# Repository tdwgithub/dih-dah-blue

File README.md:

# Dih Dah Blue

**A Bluetooth LE wireless link between a Morse code (CW) paddle and a radio.**

Dih Dah Blue replaces the cable between your CW paddle and your radio with a pair of small battery-powered boards. The paddle-side board watches the paddle contacts and sends each transition over Bluetooth LE. The radio-side board drives a solid-state relay wired to the radio's key input. To your radio, it looks like the paddle is plugged straight in.

This repository holds the firmware, KiCad schematics and PCB layouts, and the 3D-printable enclosure described in the *Circuit Cellar* article **"Dih Dah Blue – Bluetooth Remote CW Key"** by Todd Wade, W8LEV.

## How it works

Both boards are built around the Seeed Studio XIAO ESP32-C6. The module provides a RISC-V high-power (HP) core and an ultra-low-power (ULP/LP) core, a built-in LiPo charger and a USB-C port for power and programming.

| | Paddle side | Radio side |
|---|---|---|
| BLE role | Central | Peripheral (advertises as `CW_Radio`) |
| Connects to | Paddle via 3-position terminal block (left, right, common) | Radio key input via 3-position terminal block, through an ASSR-1228 2-pole solid-state relay |
| Power strategy | ULP core watches the paddle while the HP core sleeps. HP core goes to light sleep after 2 min idle and deep sleep after 10 min | HP core only, light sleep when idle |
| Typical idle current | ~90 µA | ~17 mA |

**Paddle side:** The ULP core debounces the paddle inputs, places time-stamped events on a queue shared with the HP core, then wakes the HP core. The HP core re-establishes the BLE link if needed and sends each queued event to the radio side. While the link is idle, the HP core steps down from light sleep to deep sleep. A paddle tap wakes everything back up, and the LED blinks three times quickly once the link is up.

**Radio side:** Accepts the connection, receives paddle events and drives the relay outputs to match.

## Repository layout

```
firmware/
  paddle/     ESP-IDF project: HP core (main/main.c) + ULP core (main/ulp/)
  radio/      ESP-IDF project: radio-side BLE peripheral
hardware/
  paddle/     KiCad project, schematic PDF and BOM for the paddle-side board
  radio/      KiCad project, schematic PDF and BOM for the radio-side board
  panel/      Both boards panelized into one 2-up panel, with ready-to-order Gerbers
enclosure/    OpenSCAD source and STL for the shared enclosure
docs/images/  Photos and renders
```

## Building the hardware

Each board is 2" × 2" and uses only through-hole parts. You can also build the circuits on a breadboard or stripboard.

- **Schematics:** [`hardware/paddle/Paddle-schematic.pdf`](hardware/paddle/Paddle-schematic.pdf) and [`hardware/radio/radio-schematic.pdf`](hardware/radio/radio-schematic.pdf)
- **Bills of materials:** [`hardware/paddle/Paddle-BOM.csv`](hardware/paddle/Paddle-BOM.csv) and [`hardware/radio/radio-BOM.csv`](hardware/radio/radio-BOM.csv)
- **Ordering PCBs:** Upload [`hardware/panel/dihdah_blue_r2-gerbers.zip`](hardware/panel/dihdah_blue_r2-gerbers.zip) to JLCPCB, PCBWay or a similar board house. It holds both boards on a single panel joined by mouse-bite tabs. Snap them apart and sand the edges.

**Assembly notes:**

1. Solder the low-profile parts first (resistors and capacitors), then the battery connector, then the buttons.
2. If you'll use the enclosure, bend the LED leads 90° about 1/8" above the board so the LED pokes through the enclosure hole. The cathode goes to the square pad nearest the board edge.
3. **Install the XIAO module last.** Its battery and RESET/EN and BOOT connections are only on pads underneath the module. *Before* soldering the module down, solder four wires to the **Battery +**, **Battery −**, **Reset/EN** and **Option/BOOT** pads on its underside. Route the wires out from under the edge opposite the USB-C connector. Then solder the module's header pins, trim the wires and solder them to the four labeled holes near the battery connector.

> **Article correction:** The article text says R2 and R3 are the paddle input pull-ups and R1 is the LED resistor. On both boards **R3 (1K) is the LED resistor**. On the paddle side, **R1 and R2 (100K) are the paddle input pull-ups**. The schematics (Figures 1 and 2), the PCBs and the files here are correct.

**Battery:** Either board runs from a single-cell 3.7 V LiPo (the author uses Adafruit's 500 mAh flat pack) or directly from USB-C. Buy batteries from a reputable supplier. A slot in the PCB lets the battery lead pass up from below the board.

> **Radio-side note:** The relay output is meant for "dry contact" key inputs on radios or keyers with a built-in electronic keyer. Don't connect it to older rigs that put a voltage on the key line.

## Building the firmware

Requires [ESP-IDF](https://docs.espressif.com/projects/esp-idf/en/v5.3.4/esp32c6/get-started/) **v5.3.x** (developed on v5.3.4).

```sh
cd firmware/radio        # or firmware/paddle
idf.py set-target esp32c6
idf.py build
idf.py -p <serial-port> flash monitor
```

The paddle project builds the ULP program in `main/ulp/` and embeds it into the HP-core image automatically.

To force a XIAO into the bootloader, hold **BOOT** (SW2) while pressing **RESET/EN** (SW1).

### Current limitations / ideas for future versions

- The paddle mode is fixed at NORMAL. REVERSED, IAMBIC_A and IAMBIC_B are defined but not yet selectable.
- Each event carries a timestamp, but the radio side doesn't yet use it to reconstruct paddle timing.
- Settings could be made configurable through the BOOT button, a serial console or a phone app.

## Enclosure

[`enclosure/dihdah_blue_enclosure.scad`](enclosure/dihdah_blue_enclosure.scad) is a parametric OpenSCAD design (Listing 1 in the article). It fits either board, and [`dihdah_blue_enclosure.stl`](enclosure/dihdah_blue_enclosure.stl) is ready to slice. GitHub shows the STL in a 3D viewer.

- PCB mounting: M3 × 8 mm pan-head self-tapping screws
- Lid: M2.5 × 8 mm countersunk self-tapping screws
- The design isn't meant for repeated opening. Switch to brass heat-set inserts and machine screws if you'll open it often.

## License

- **Firmware** (`firmware/`): [MIT](LICENSE)
- **Hardware and enclosure** (`hardware/`, `enclosure/`): [CERN-OHL-P-2.0](hardware/LICENSE)

© 2024–2026 Todd D. Wade, W8LEV

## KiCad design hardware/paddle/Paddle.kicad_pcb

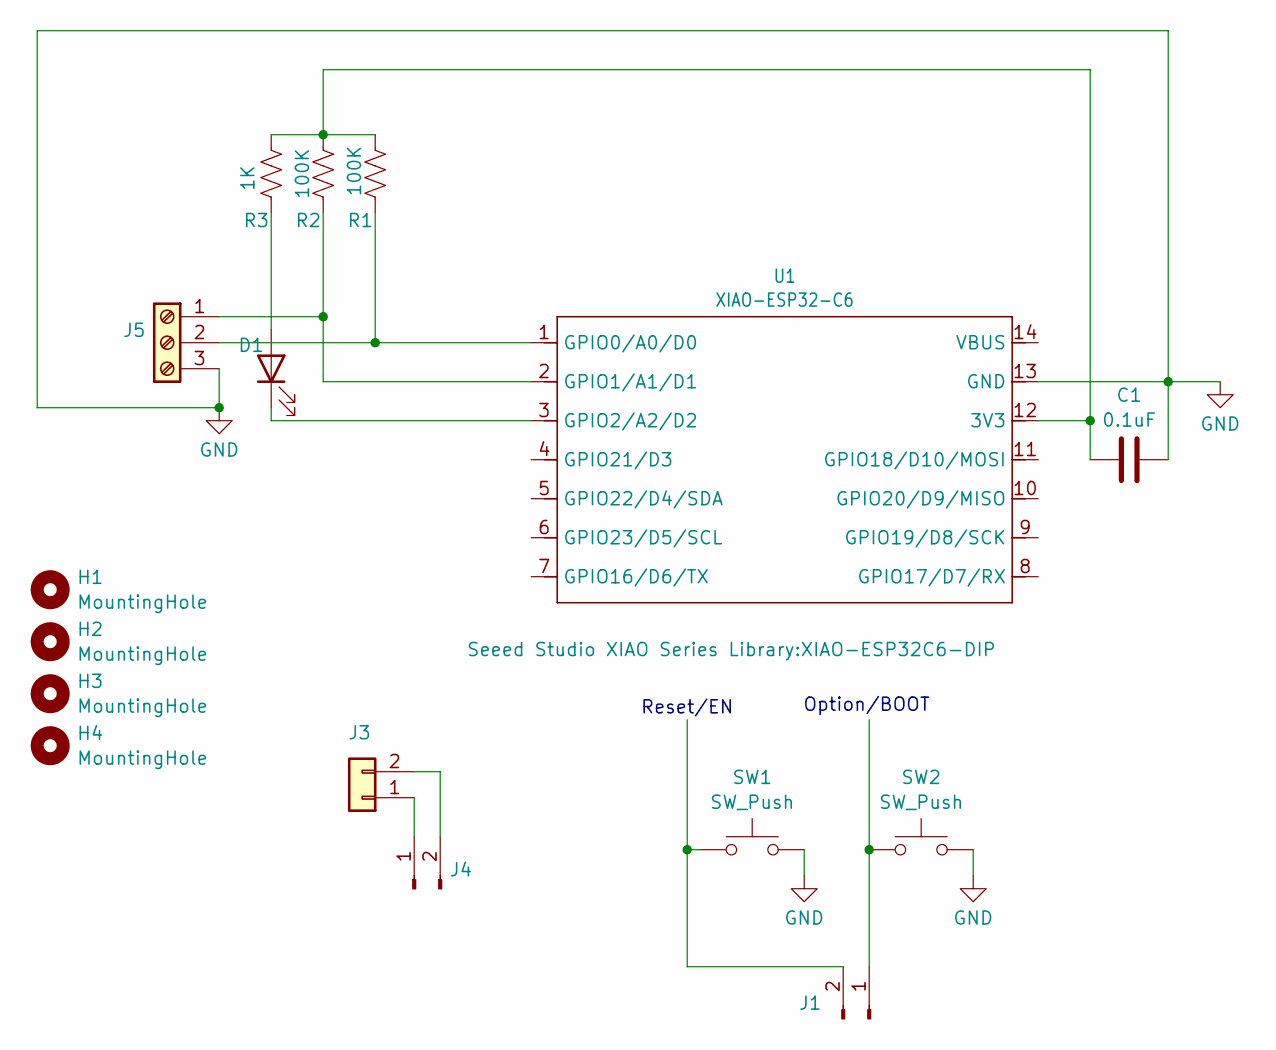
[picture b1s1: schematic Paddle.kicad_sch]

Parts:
C1: 0.1uF; C_Disc_D3.0mm_W1.6mm_P2.50mm
D1: LED_D3.0mm_Horizontal_O1.27mm_Z6.0mm
H1, H2, H3, H4: MountingHole; MountingHole_3.5mm
J1, J4: Conn_01x02_Pin; PinHeader_1x02_P2.54mm_Vertical
J3: Conn_01x02; JST_PH_S2B-PH-K_1x02_P2.00mm_Horizontal
J5: Screw_Terminal_01x03; 691313510003
R1, R2: 100K; R_Axial_DIN0207_L6.3mm_D2.5mm_P10.16mm_Horizontal
R3: 1K; R_Axial_DIN0207_L6.3mm_D2.5mm_P10.16mm_Horizontal
SW1, SW2: SW_Push; SW_Tactile_SPST_Angled_PTS645Vx83-2LFS
U1: XIAO-ESP32-C6; XIAO-ESP32C6-DIP

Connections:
GND: C1.1, J5.3, SW1.1, SW2.2, U1.13 (GND)
unnamed: D1.2 (A), R3.2
unnamed: D1.1 (K), U1.3 (GPIO2/A2/D2)
unnamed: J1.1, SW2.1
unnamed: J1.2, SW1.2
unnamed: J3.1, J4.1
unnamed: J3.2, J4.2
unnamed: J5.1, R2.2, U1.2 (GPIO1/A1/D1)
unnamed: J5.2, R1.2, U1.1 (GPIO0/A0/D0)
unnamed: C1.2, R1.1, R2.1, R3.1, U1.12 (3V3)

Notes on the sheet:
Reset/EN
Option/BOOT

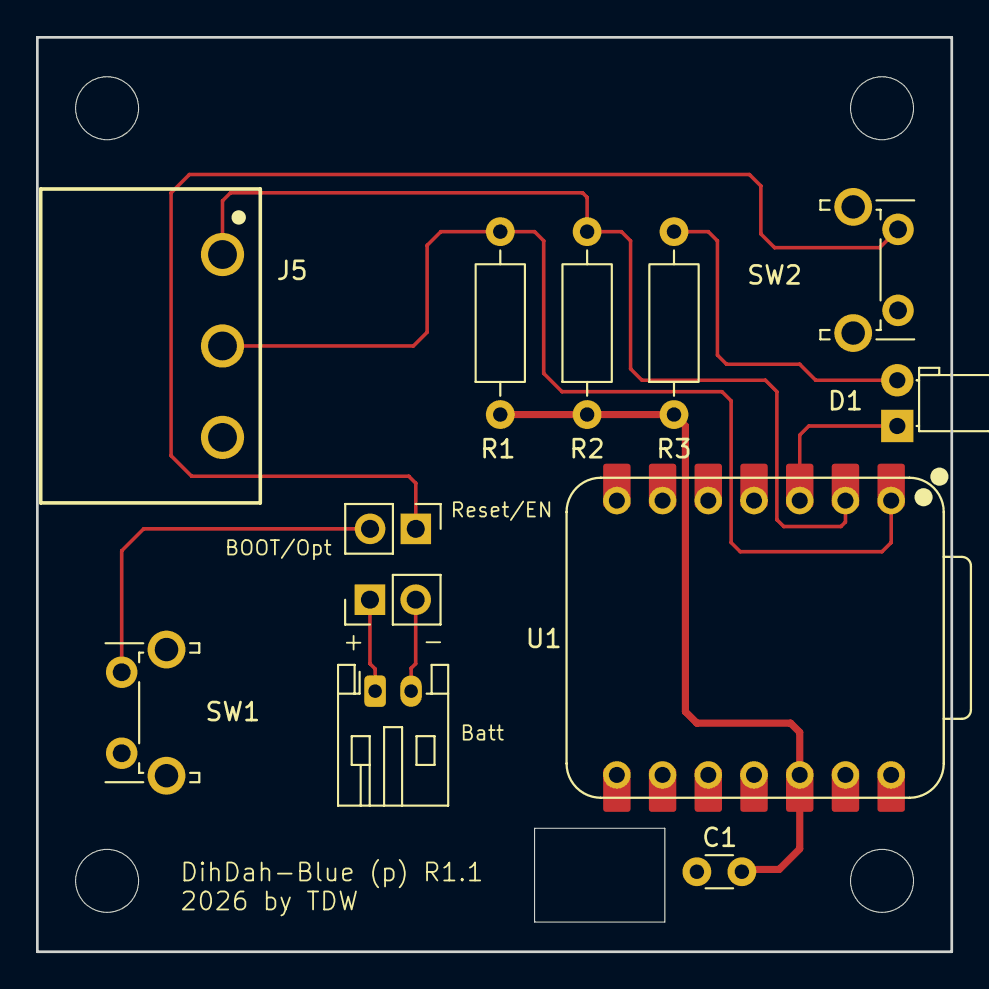
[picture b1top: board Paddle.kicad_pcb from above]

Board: 2 copper layers, 50.8 x 50.8 mm, 16 parts (0 on the bottom side), 10 nets.

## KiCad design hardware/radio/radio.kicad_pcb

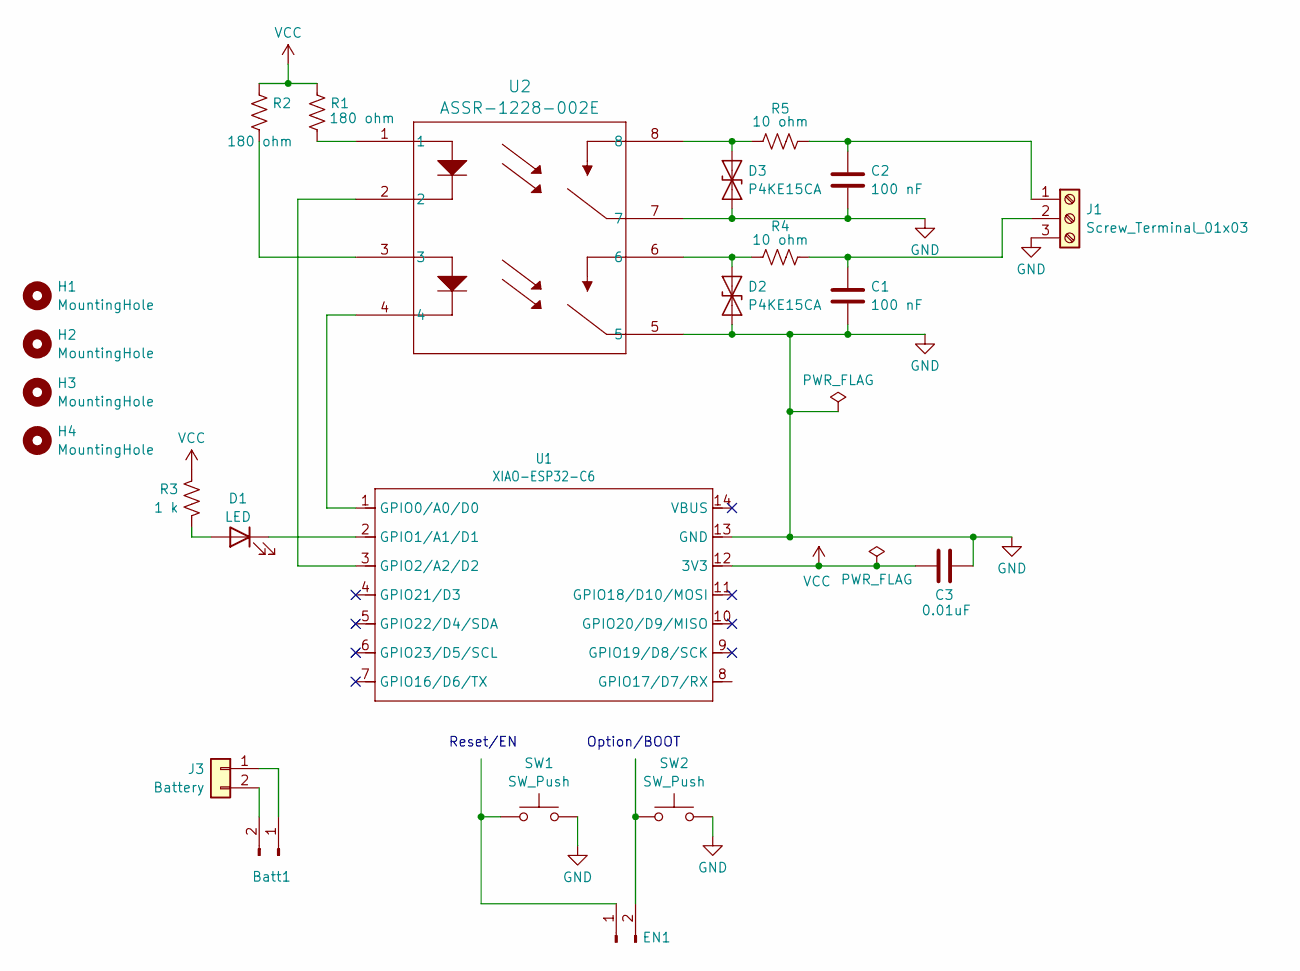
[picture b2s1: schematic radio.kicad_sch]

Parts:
Batt1: Conn_01x02_Pin; PinHeader_1x02_P2.54mm_Vertical
C1, C2: 100 nF; C_Disc_D5.0mm_W2.5mm_P5.00mm
C3: 0.01uF; C_Disc_D3.0mm_W1.6mm_P2.50mm
D1: LED; LED_D3.0mm_Horizontal_O1.27mm_Z6.0mm
D2, D3: P4KE15CA; D_DO-41_SOD81_P10.16mm_Horizontal
EN1: Conn_01x02_Pin; PinHeader_1x02_P2.54mm_Vertical
H1, H2, H3, H4: MountingHole; MountingHole_3.5mm
J1: Screw_Terminal_01x03; 691313510003
J3: Battery; JST_PH_S2B-PH-K_1x02_P2.00mm_Horizontal
R1, R2: 180 ohm; R_Axial_DIN0207_L6.3mm_D2.5mm_P10.16mm_Horizontal
R3: 1 k; R_Axial_DIN0207_L6.3mm_D2.5mm_P10.16mm_Horizontal
R4, R5: 10 ohm; R_Axial_DIN0207_L6.3mm_D2.5mm_P10.16mm_Horizontal
SW1, SW2: SW_Push; SW_Tactile_SPST_Angled_PTS645Vx83-2LFS
U1: XIAO-ESP32-C6; XIAO-ESP32C6-DIP
U2: ASSR-1228-002E; DIP-8_W7.62mm

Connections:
GND: C1.2, C2.2, C3.1, D2.2 (A2), D3.2 (A2), J1.3, SW1.2, SW2.1, U1.13 (GND), U2.5, U2.7
unnamed: Batt1.1, J3.1
unnamed: Batt1.2, J3.2
unnamed: D1.2 (A), R3.2
unnamed: D1.1 (K), U1.2 (GPIO1/A1/D1)
unnamed: D2.1 (A1), R4.2, U2.6
unnamed: D3.1 (A1), R5.2, U2.8
unnamed: EN1.1, SW1.1
unnamed: EN1.2, SW2.2
unnamed: C2.1, J1.1, R5.1
unnamed: C1.1, J1.2, R4.1
unnamed: R1.2, U2.1
unnamed: R2.2, U2.3
unnamed: U1.1 (GPIO0/A0/D0), U2.4
unnamed: U1.3 (GPIO2/A2/D2), U2.2
VCC: C3.2, R1.1, R2.1, R3.1, U1.12 (3V3)

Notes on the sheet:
Reset/EN
Option/BOOT

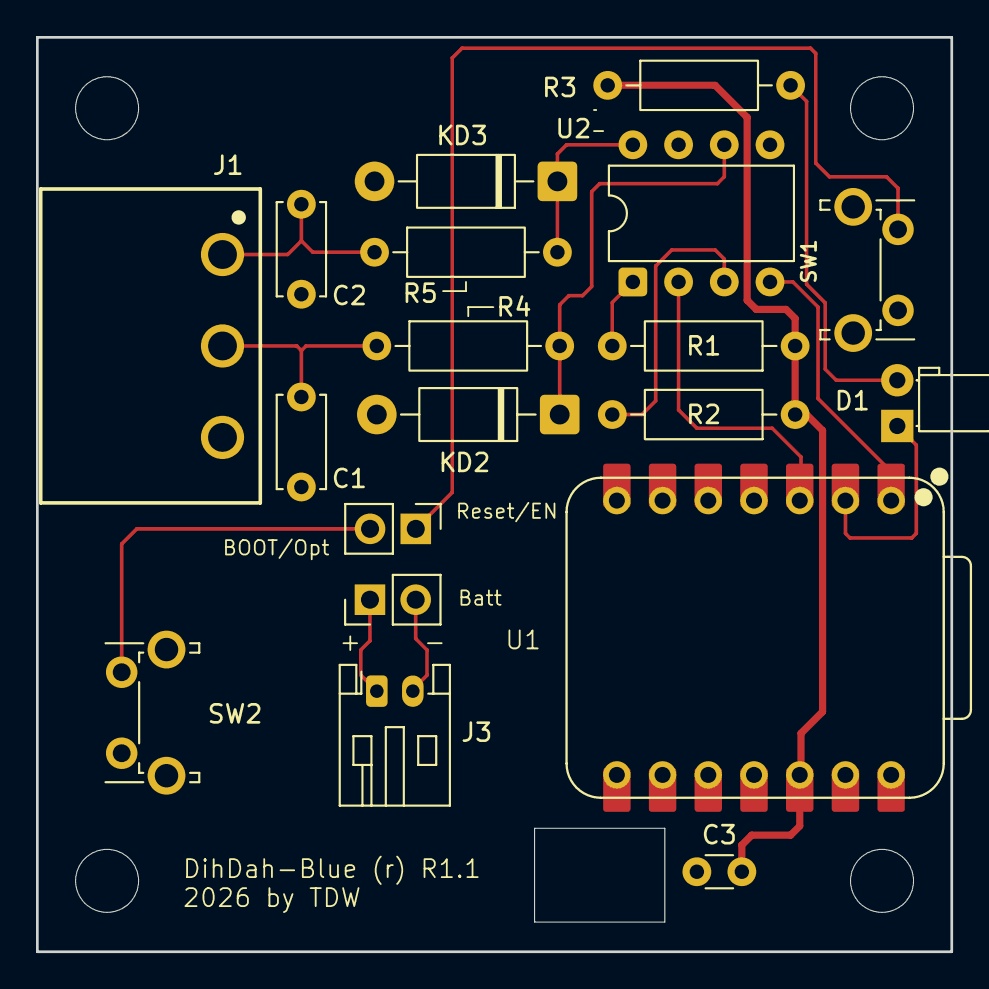
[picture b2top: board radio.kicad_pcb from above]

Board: 2 copper layers, 50.8 x 50.8 mm, 23 parts (0 on the bottom side), 16 nets.

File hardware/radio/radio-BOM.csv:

"Refs","Value","Footprint","Qty","Datasheet"
"Batt1,EN1","Conn_01x02_Pin","Connector_PinHeader_2.54mm:PinHeader_1x02_P2.54mm_Vertical","2","~"
"C1,C2","100 nF","Capacitor_THT:C_Disc_D5.0mm_W2.5mm_P5.00mm","2","~"
"C3","0.01uF","Capacitor_THT:C_Disc_D3.0mm_W1.6mm_P2.50mm","1","~"
"D1","LED","LED_THT:LED_D3.0mm_Horizontal_O1.27mm_Z6.0mm","1","~"
"D2,D3","P4KE15CA","Diode_THT:D_DO-41_SOD81_P10.16mm_Horizontal","2",""
"J1","Screw_Terminal_01x03","Wurth:691313510003","1","~"
"J3","Battery","Connector_JST:JST_PH_S2B-PH-K_1x02_P2.00mm_Horizontal","1","~"
"R1,R2","180 ohm","Resistor_THT:R_Axial_DIN0207_L6.3mm_D2.5mm_P10.16mm_Horizontal","2","~"
"R3","1 k","Resistor_THT:R_Axial_DIN0207_L6.3mm_D2.5mm_P10.16mm_Horizontal","1","~"
"R4,R5","10 ohm","Resistor_THT:R_Axial_DIN0207_L6.3mm_D2.5mm_P10.16mm_Horizontal","2","~"
"SW1,SW2","SW_Push","Button_Switch_THT:SW_Tactile_SPST_Angled_PTS645Vx83-2LFS","2","~"
"U1","XIAO-ESP32-C6","Seeed Studio XIAO Series Library:XIAO-ESP32C6-DIP","1",""
"U2","ASSR-1228-002E","Package_DIP:DIP-8_W7.62mm","1","ASSR-1228-002E"
